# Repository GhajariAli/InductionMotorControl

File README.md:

# InductionMotorControl
Controlling 3 Phase AC Asynchronous Induction Motor

Check [This](https://github.com/GhajariAli/DCMotorControl) Repo for DC motor Control

<details>
<summary> Preparation </summary>
  
  <details>
    
  <summary> Motor Nameplate </summary>

  </details>
  
  <details>
    
  <summary> Designing the circuit </summary>
  
  I've Designed the control boad around this IC fro Infineon [IGCM04F60GAXKMA1](https://www.digikey.ca/en/products/detail/infineon-technologies/IGCM04F60GAXKMA1/5960098)
  
  Here is the video of testing the circuit and getting initial result:
  
   [ ](https://www.youtube.com/shorts/fg0to3o2meA)
  
  So I designed a PCB to get things going Faster, you can find the KiCAD design and initial code to run the motor in [THIS](https://github.com/GhajariAli/InductionMotorControl/tree/FirstCurcuitDesign) branch

  </details>
  
  <details>
    
  <summary> Adding Encoder </summary>
  Induction Motors are usally not controlled by a closed loop using encoder but to validate and verify my own work I'd like to have and encoder on the shaft.
  
  [here](https://www.aliexpress.com/item/4000094589182.html?spm=a2g0o.order_list.order_list_main.56.1fdd1802ZbFUS8) is the encoder I've used : 

  Below is what I've designed to mount the encoder, you'll find all 3D models in the same branch as mentioned in the circuit diagram section.

  Update: had to dessign and print the belt with TPU as it was not standard size turned out good:

  </details>

  <details>
    
  <summary> Testing the PCB </summary>
  PCB came very good. had to change couple resistors and design a base for it:

  and IT WORKS THE FIRST TRY!
  </details>
</details>

<details>
<summary> SPWM speed Control </summary>
  Here is the low and high side signals with only Hi side SPWM:

  and here is the final output 3phase

  this made the motor run smoother, current is now lower and it makes less noise.
  
  This was great but the curent of the motor was not sinusoidal at all.

  Terrible waveform:

  the reason is behind this picture

  so the high and low are not equal value. So it's required to add low side SPWM as well
  Here is the gate signals with all SPWM

  A Closer look

  Here is how the SPWM signals on the High side look after passing through a Filter:

  Now motor current is much more close to sinusoidal current

  here is how the syncronous speed, actual speed and slip looks like in a ramp to 50HZ and coast to stop. as you can see it's not great yet, need to source more voltage (currently only have 60VDC), I believe the V/F control can't go all the way to 50hz with 60 volt.

</details>

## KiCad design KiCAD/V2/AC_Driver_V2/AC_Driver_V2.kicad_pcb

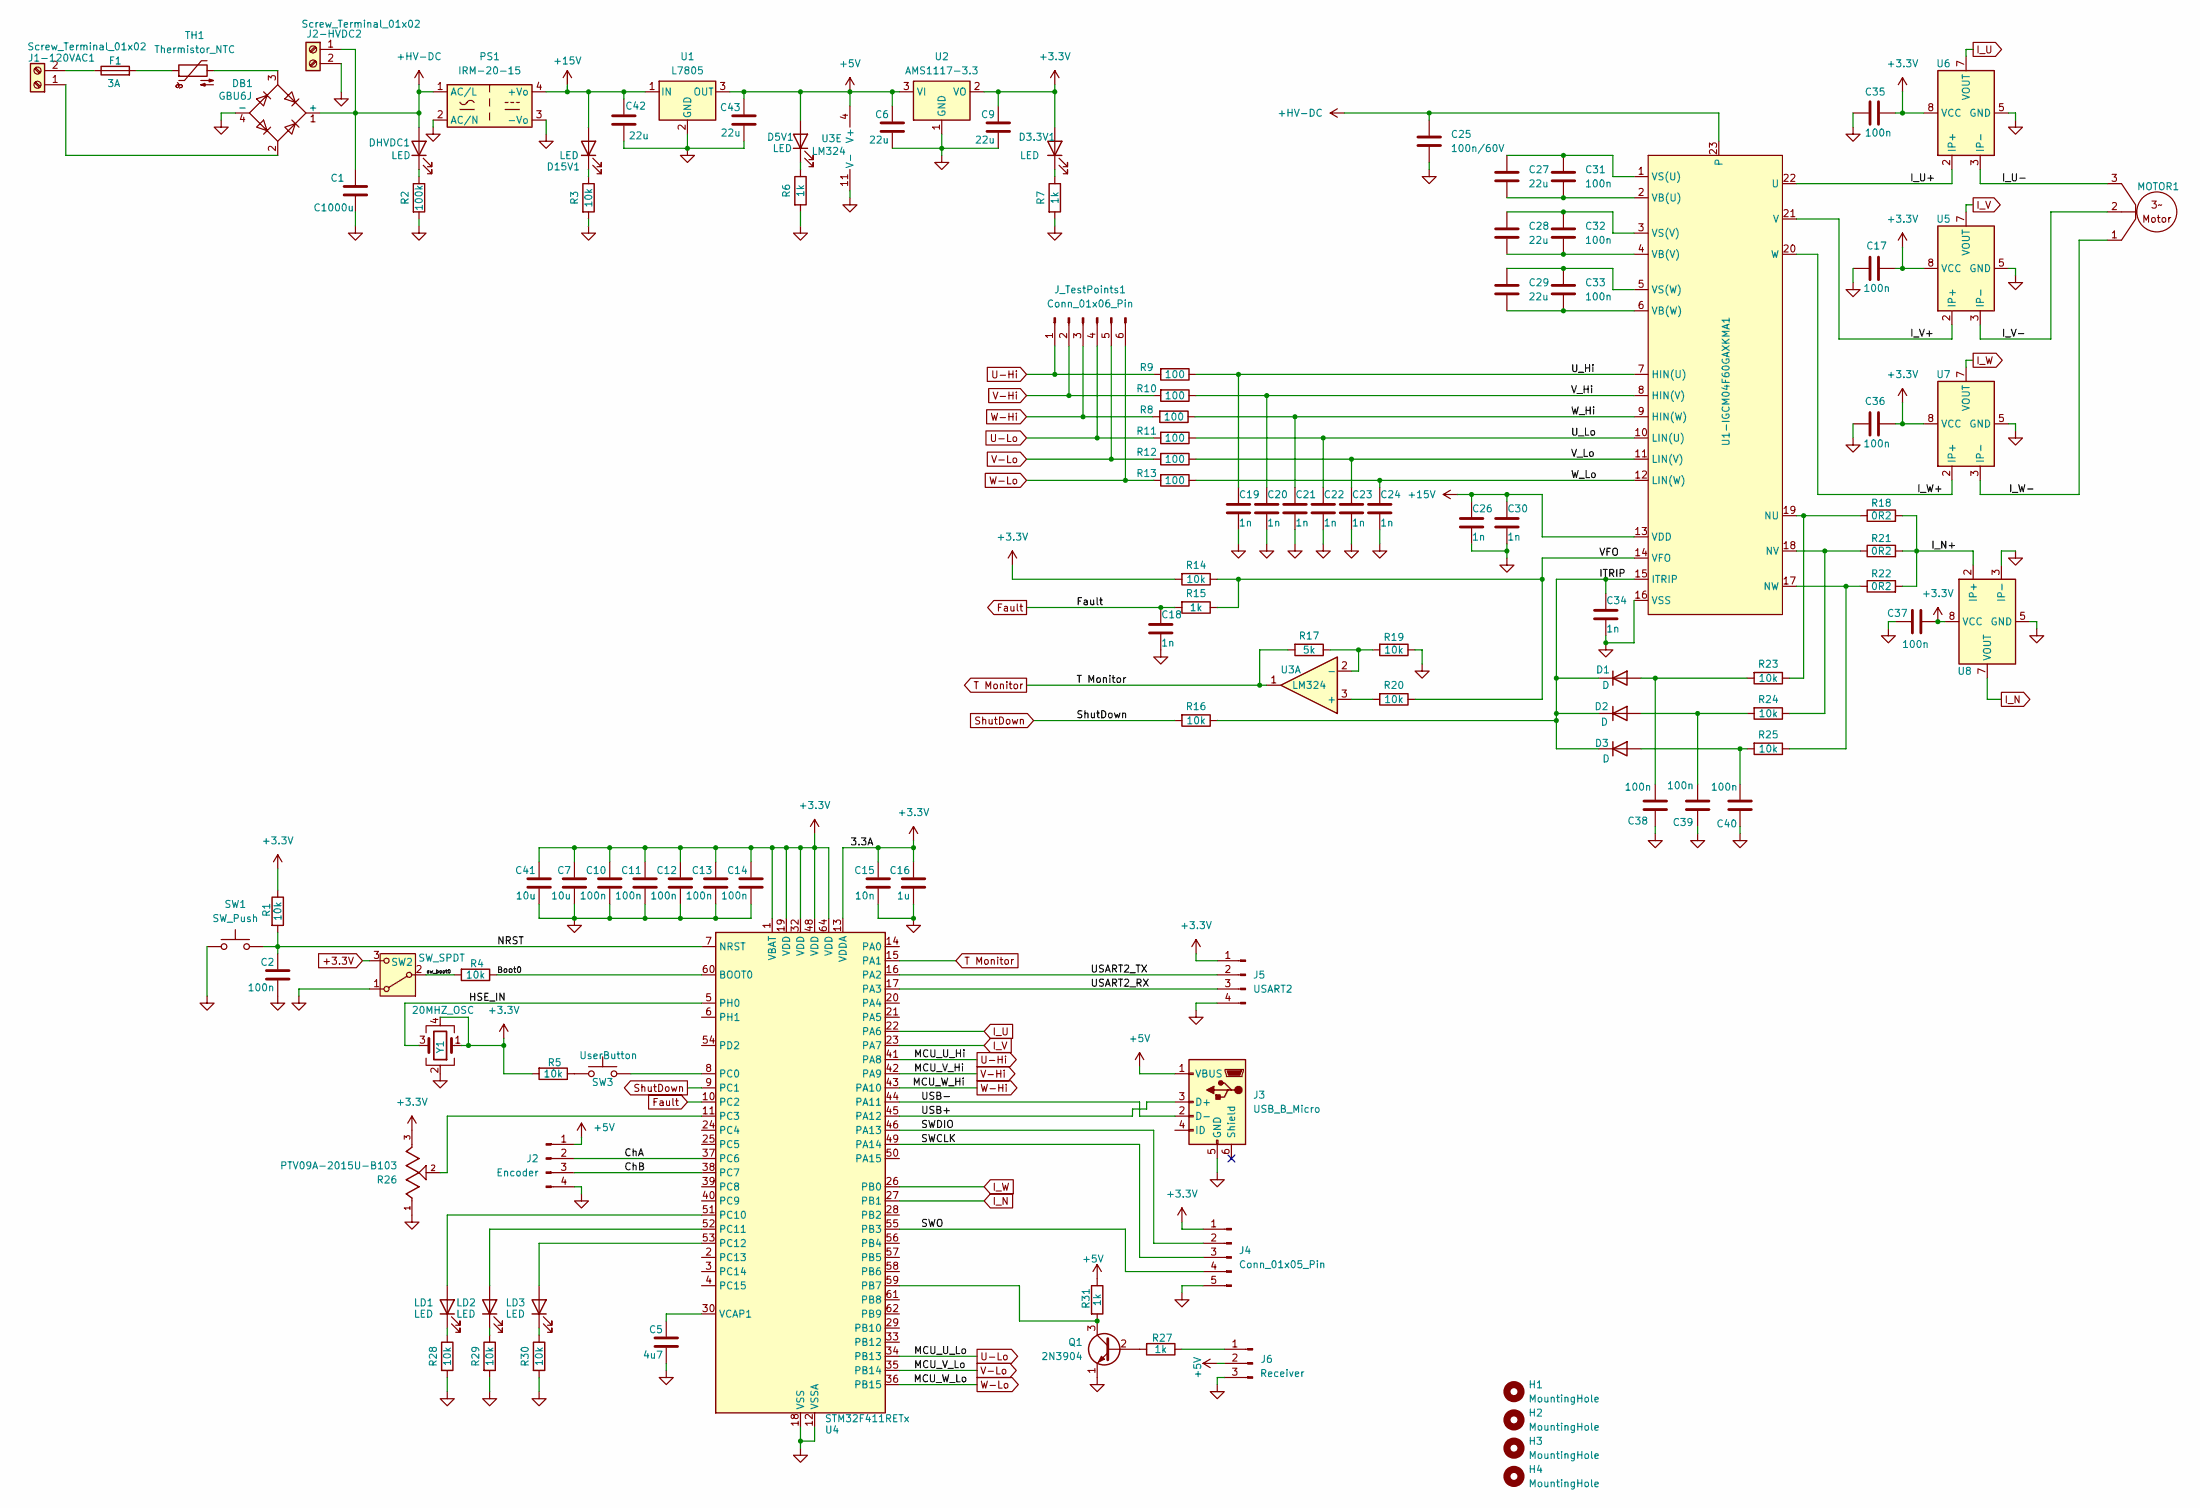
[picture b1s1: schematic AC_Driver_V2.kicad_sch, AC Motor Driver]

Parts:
C1: C1000u; CP_Radial_D22.0mm_P10.00mm_SnapIn
C2, C10, C11, C12, C13, C14, C17, C31, C32, C33, C35, C36, C37, C38, C39, C40: 100n; C_0805_2012Metric
C5: 4u7; C_0805_2012Metric
C6, C9, C42, C43: 22u; C_0805_2012Metric
C7, C41: 10u; C_0805_2012Metric
C15: 10n; C_0805_2012Metric
C16: 1u; C_0805_2012Metric
C18, C19, C20, C21, C22, C23, C24, C26, C30, C34: 1n; C_0805_2012Metric
C25: 100n/60V; C_0805_2012Metric
C27, C28, C29: 22u; C_Radial_D4.0mm_H7.0mm_P1.50mm
D1, D2, D3: D; L_1206_3216Metric
D3.3V1, D5V1, D15V1: LED; LED_0805_2012Metric
DB1: GBU6J; Diode_Bridge_Vishay_GBU
DHVDC1: LED; LED_0805_2012Metric
F1: 3A; L_2512_6332Metric
H1, H2, H3, H4: MountingHole; MountingHole_3.2mm_M3_Pad_Via
J1-120VAC1, J2-HVDC2: Screw_Terminal_01x02; TerminalBlock_Phoenix_PT-1,5-2-5.0-H_1x02_P5.00mm_Horizontal
J2: Encoder; PinHeader_1x04_P2.54mm_Vertical
J3: USB_B_Micro; USB_Micro-B_Amphenol_10103594-0001LF_Horizontal
J4: Conn_01x05_Pin; PinHeader_1x05_P2.54mm_Vertical
J5: USART2; PinHeader_1x04_P2.54mm_Vertical
J6: Receiver; PinHeader_1x03_P2.54mm_Vertical
J_TestPoints1: Conn_01x06_Pin; PinHeader_1x06_P2.54mm_Vertical
LD1, LD2, LD3: LED; LED_0805_2012Metric
MOTOR1: TerminalBlock_Phoenix_PT-1,5-3-5.0-H_1x03_P5.00mm_Horizontal
PS1: IRM-20-15; Converter_ACDC_MeanWell_IRM-20-xx_THT
Q1: 2N3904; TO-92_Inline
R1, R3, R4, R5, R14, R16, R19, R20, R23, R24, R25, R28, R29, R30: 10k; R_0805_2012Metric
R2: 100k; R_0805_2012Metric
R6, R7, R15, R27, R31: 1k; R_0805_2012Metric
R8, R9, R10, R11, R12, R13: 100; R_0805_2012Metric
R17: 5k; R_0805_2012Metric
R18, R21, R22: 0R2; R_Axial_DIN0309_L9.0mm_D3.2mm_P2.54mm_Vertical
R26: PTV09A-2015U-B103; TRIM_PTV09A-2015U-B103; PARTREV 01/20
SW1: SW_Push; SW_Push_1TS009xxxx-xxxx-xxxx_6x6x5mm
SW2: SW_SPDT; SW_SPDT_PCM12
SW3: UserButton; SW_Push_1TS009xxxx-xxxx-xxxx_6x6x5mm
TH1: Thermistor_NTC; R_Axial_DIN0414_L11.9mm_D4.5mm_P7.62mm_Vertical
U1: L7805; TO-263-3_TabPin2
U1-IGCM04F60GAXKMA1: IGCM04F60GAXKMA1
U2: AMS1117-3.3; SOT-223-3_TabPin2
U3: LM324; SSOP-14_5.3x6.2mm_P0.65mm
U4: STM32F411RETx; LQFP-64_10x10mm_P0.5mm
U5, U6, U7, U8: ACS706xLC-05C; SOIC-8_3.9x4.9mm_P1.27mm
Y1: 20MHZ_OSC; Crystal_SMD_Abracon_ABM3C-4Pin_5.0x3.2mm

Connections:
+3.3V: C7.1, C9.1, C10.1, C11.1, C12.1, C13.1, C14.1, C15.1, C16.1, C17.1, C35.1, C36.1, C37.2, C41.1, D3.3V1.2 (A), J4.1, J5.1, R1.1, R5.2, R14.2, R26.3, SW2.3 (C), U2.2 (VO), U4.1 (VBAT), U4.13 (VDDA), U4.19 (VDD), U4.32 (VDD), U4.48 (VDD), U4.64 (VDD), U5.8 (VCC), U6.8 (VCC), U7.8 (VCC), U8.8 (VCC), Y1.1, Y1.4; also elsewhere on the board
+5V: C6.1, C43.1, D5V1.2 (A), J2.1, J3.1 (VBUS), J6.2, R31.1, U1.3 (OUT), U2.3 (VI), U3.4 (V+); also elsewhere on the board
+15V: C26.1, C30.1, C42.1, D15V1.2 (A), PS1.4 (+Vo), U1.1 (IN), U1-IGCM04F60GAXKMA1.13 (VDD); also elsewhere on the board
+HV-DC: C1.1, C25.1, DB1.1 (+), DHVDC1.2 (A), J2-HVDC2.1, PS1.1 (AC/L), U1-IGCM04F60GAXKMA1.23; also elsewhere on the board
/Boot0: R4.1, U4.60 (BOOT0)
/ChA: J2.2, U4.37 (PC6)
/ChB: J2.3, U4.38 (PC7)
/HSE_IN: U4.5 (PH0), Y1.3
/ITRIP: C34.1, D1.1 (K), D2.1 (K), D3.1 (K), R16.1, U1-IGCM04F60GAXKMA1.15 (ITRIP)
/I_N+: R18.2, R21.2, R22.2, U8.1 (IP+), U8.2 (IP+)
/I_U+: U1-IGCM04F60GAXKMA1.22 (U), U6.1 (IP+), U6.2 (IP+)
/I_U-: MOTOR1.3 (W), U6.3 (IP-), U6.4 (IP-)
/I_V+: U1-IGCM04F60GAXKMA1.21 (V), U5.1 (IP+), U5.2 (IP+)
/I_V-: MOTOR1.2 (V), U5.3 (IP-), U5.4 (IP-)
/I_W+: U1-IGCM04F60GAXKMA1.20 (W), U7.1 (IP+), U7.2 (IP+)
/I_W-: MOTOR1.1 (U), U7.3 (IP-), U7.4 (IP-)
/NRST: C2.1, R1.2, SW1.2, U4.7 (NRST)
/SWCLK: J4.3, U4.49 (PA14)
/SWDIO: J4.2, U4.46 (PA13)
/SWO: J4.4, U4.55 (PB3)
/USART2_RX: J5.3, U4.17 (PA3)
/USART2_TX: J5.2, U4.16 (PA2)
/USB+: J3.3 (D+), U4.45 (PA12)
/USB-: J3.2 (D-), U4.44 (PA11)
/U_Hi: C19.1, R9.1, U1-IGCM04F60GAXKMA1.7 (HIN(U))
/U_Lo: C22.1, R11.1, U1-IGCM04F60GAXKMA1.10 (LIN(U))
/VFO: R14.1, R15.1, R20.1, U1-IGCM04F60GAXKMA1.14 (VFO)
/V_Hi: C20.1, R10.1, U1-IGCM04F60GAXKMA1.8 (HIN(V))
/V_Lo: C23.1, R12.1, U1-IGCM04F60GAXKMA1.11 (LIN(V))
/W_Hi: C21.1, R8.1, U1-IGCM04F60GAXKMA1.9 (HIN(W))
/W_Lo: C24.1, R13.1, U1-IGCM04F60GAXKMA1.12 (LIN(W))
/sw_boot0: R4.2, SW2.2 (B)
Fault: C18.1, R15.2, U4.10 (PC2)
GND: C1.2, C2.2, C5.2, C6.2, C7.2, C9.2, C10.2, C11.2, C12.2, C13.2, C14.2, C15.2, C16.2, C17.2, C18.2, C19.2, C20.2, C21.2, C22.2, C23.2, C24.2, C25.2, C26.2, C30.2, C34.2, C35.2, C36.2, C37.1, C38.1, C39.1, C40.1, C41.2, C42.2, C43.2, DB1.4 (-), J2.4, J2-HVDC2.2, J3.5 (GND), J4.5, J5.4, J6.3, PS1.2 (AC/N), PS1.3 (-Vo), Q1.1 (E), R2.2, R3.2, R6.2, R7.2, R19.1, R26.1, R28.2, R29.2, R30.2, SW1.1, SW2.1 (A), U1.2 (GND), U1-IGCM04F60GAXKMA1.16 (VSS), U2.1 (GND), U3.11 (V-), U4.12 (VSSA), U4.18 (VSS), U4.31 (VSS), U4.47 (VSS), U4.63 (VSS), U5.5 (GND), U6.5 (GND), U7.5 (GND), U8.3 (IP-), U8.4 (IP-), U8.5 (GND), Y1.2; also elsewhere on the board
I_N: U4.27 (PB1), U8.7 (VOUT); also elsewhere on the board
I_U: U4.22 (PA6), U6.7 (VOUT); also elsewhere on the board
I_V: U4.23 (PA7), U5.7 (VOUT); also elsewhere on the board
I_W: U4.26 (PB0), U7.7 (VOUT); also elsewhere on the board
unnamed: C38.2, D1.2 (A), R23.2
unnamed: C39.2, D2.2 (A), R24.2
unnamed: C40.2, D3.2 (A), R25.2
unnamed: D3.3V1.1 (K), R7.1
unnamed: D5V1.1 (K), R6.1
unnamed: D15V1.1 (K), R3.1
unnamed: DB1.3, TH1.2
unnamed: DHVDC1.1 (K), R2.1
unnamed: F1.2, TH1.1
unnamed: DB1.2, J1-120VAC1.1
unnamed: F1.1, J1-120VAC1.2
unnamed: J6.1, R27.1
unnamed: LD1.2 (A), U4.51 (PC10)
unnamed: LD1.1 (K), R28.1
unnamed: LD2.2 (A), U4.52 (PC11)
unnamed: LD2.1 (K), R29.1
unnamed: LD3.2 (A), U4.53 (PC12)
unnamed: LD3.1 (K), R30.1
unnamed: Q1.2 (B), R27.2
unnamed: Q1.3 (C), R31.2, U4.59 (PB7)
unnamed: R5.1, SW3.1
unnamed: R18.1, R23.1, U1-IGCM04F60GAXKMA1.19 (NU)
unnamed: R21.1, R24.1, U1-IGCM04F60GAXKMA1.18 (NV)
unnamed: R22.1, R25.1, U1-IGCM04F60GAXKMA1.17 (NW)
unnamed: C27.2, C31.2, U1-IGCM04F60GAXKMA1.2 (VB(U))
unnamed: C28.2, C32.2, U1-IGCM04F60GAXKMA1.4 (VB(V))
unnamed: C29.2, C33.2, U1-IGCM04F60GAXKMA1.6 (VB(W))
unnamed: C27.1, C31.1, U1-IGCM04F60GAXKMA1.1 (VS(U))
unnamed: C28.1, C32.1, U1-IGCM04F60GAXKMA1.3 (VS(V))
unnamed: C29.1, C33.1, U1-IGCM04F60GAXKMA1.5 (VS(W))
unnamed: R20.2, U3.3 (+)
unnamed: R17.1, R19.2, U3.2 (-)
unnamed: SW3.2, U4.8 (PC0)
unnamed: R26.2, U4.11 (PC3)
unnamed: C5.1, U4.30 (VCAP1)
ShutDown: R16.2, U4.9 (PC1)
T Monitor: R17.2, U3.1, U4.15 (PA1)
U-Hi: J_TestPoints1.1, R9.2, U4.41 (PA8)
U-Lo: J_TestPoints1.4, R11.2, U4.34 (PB13)
V-Hi: J_TestPoints1.2, R10.2, U4.42 (PA9)
V-Lo: J_TestPoints1.5, R12.2, U4.35 (PB14)
W-Hi: J_TestPoints1.3, R8.2, U4.43 (PA10)
W-Lo: J_TestPoints1.6, R13.2, U4.36 (PB15)

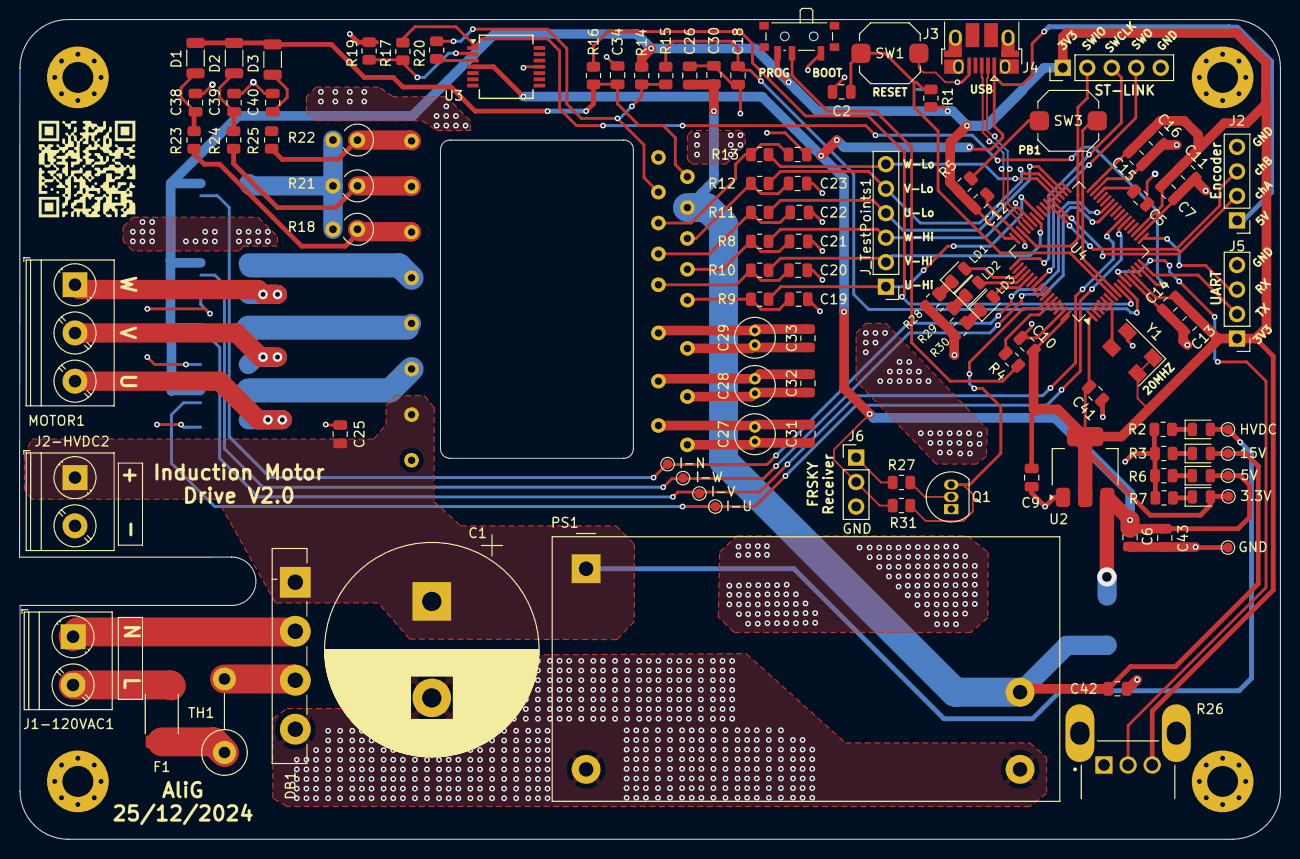
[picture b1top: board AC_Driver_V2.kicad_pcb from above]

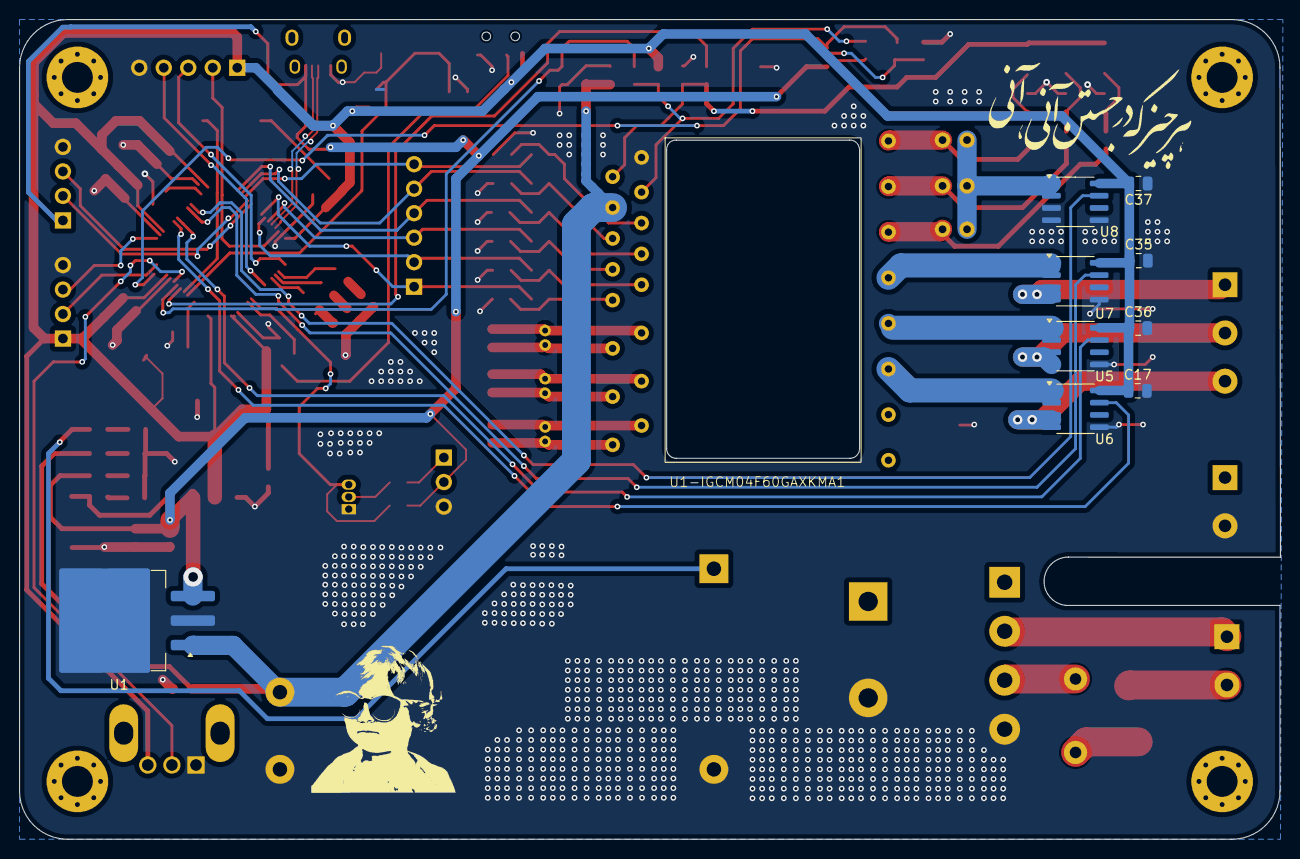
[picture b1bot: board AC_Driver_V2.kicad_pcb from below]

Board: 2 copper layers, 130.8 x 85.0 mm, 121 parts (10 on the bottom side), 81 nets.

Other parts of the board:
3.3V, 5V, 15V: TestPoint_Pad_D1.0mm
GND: TestPoint_Pad_D1.0mm
HVDC: TestPoint_Pad_D1.0mm
I-N: TestPoint_Pad_D1.0mm
I-U: TestPoint_Pad_D1.0mm
I-V: TestPoint_Pad_D1.0mm
I-W: TestPoint_Pad_D1.0mm

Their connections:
+3.3V: 3.3V.1; also elsewhere on the board
+5V: 5V.1; also elsewhere on the board
+15V: 15V.1; also elsewhere on the board
+HV-DC: HVDC.1; also elsewhere on the board
GND: GND.1; also elsewhere on the board
I_N: I-N.1; also elsewhere on the board
I_U: I-U.1; also elsewhere on the board
I_V: I-V.1; also elsewhere on the board
I_W: I-W.1; also elsewhere on the board

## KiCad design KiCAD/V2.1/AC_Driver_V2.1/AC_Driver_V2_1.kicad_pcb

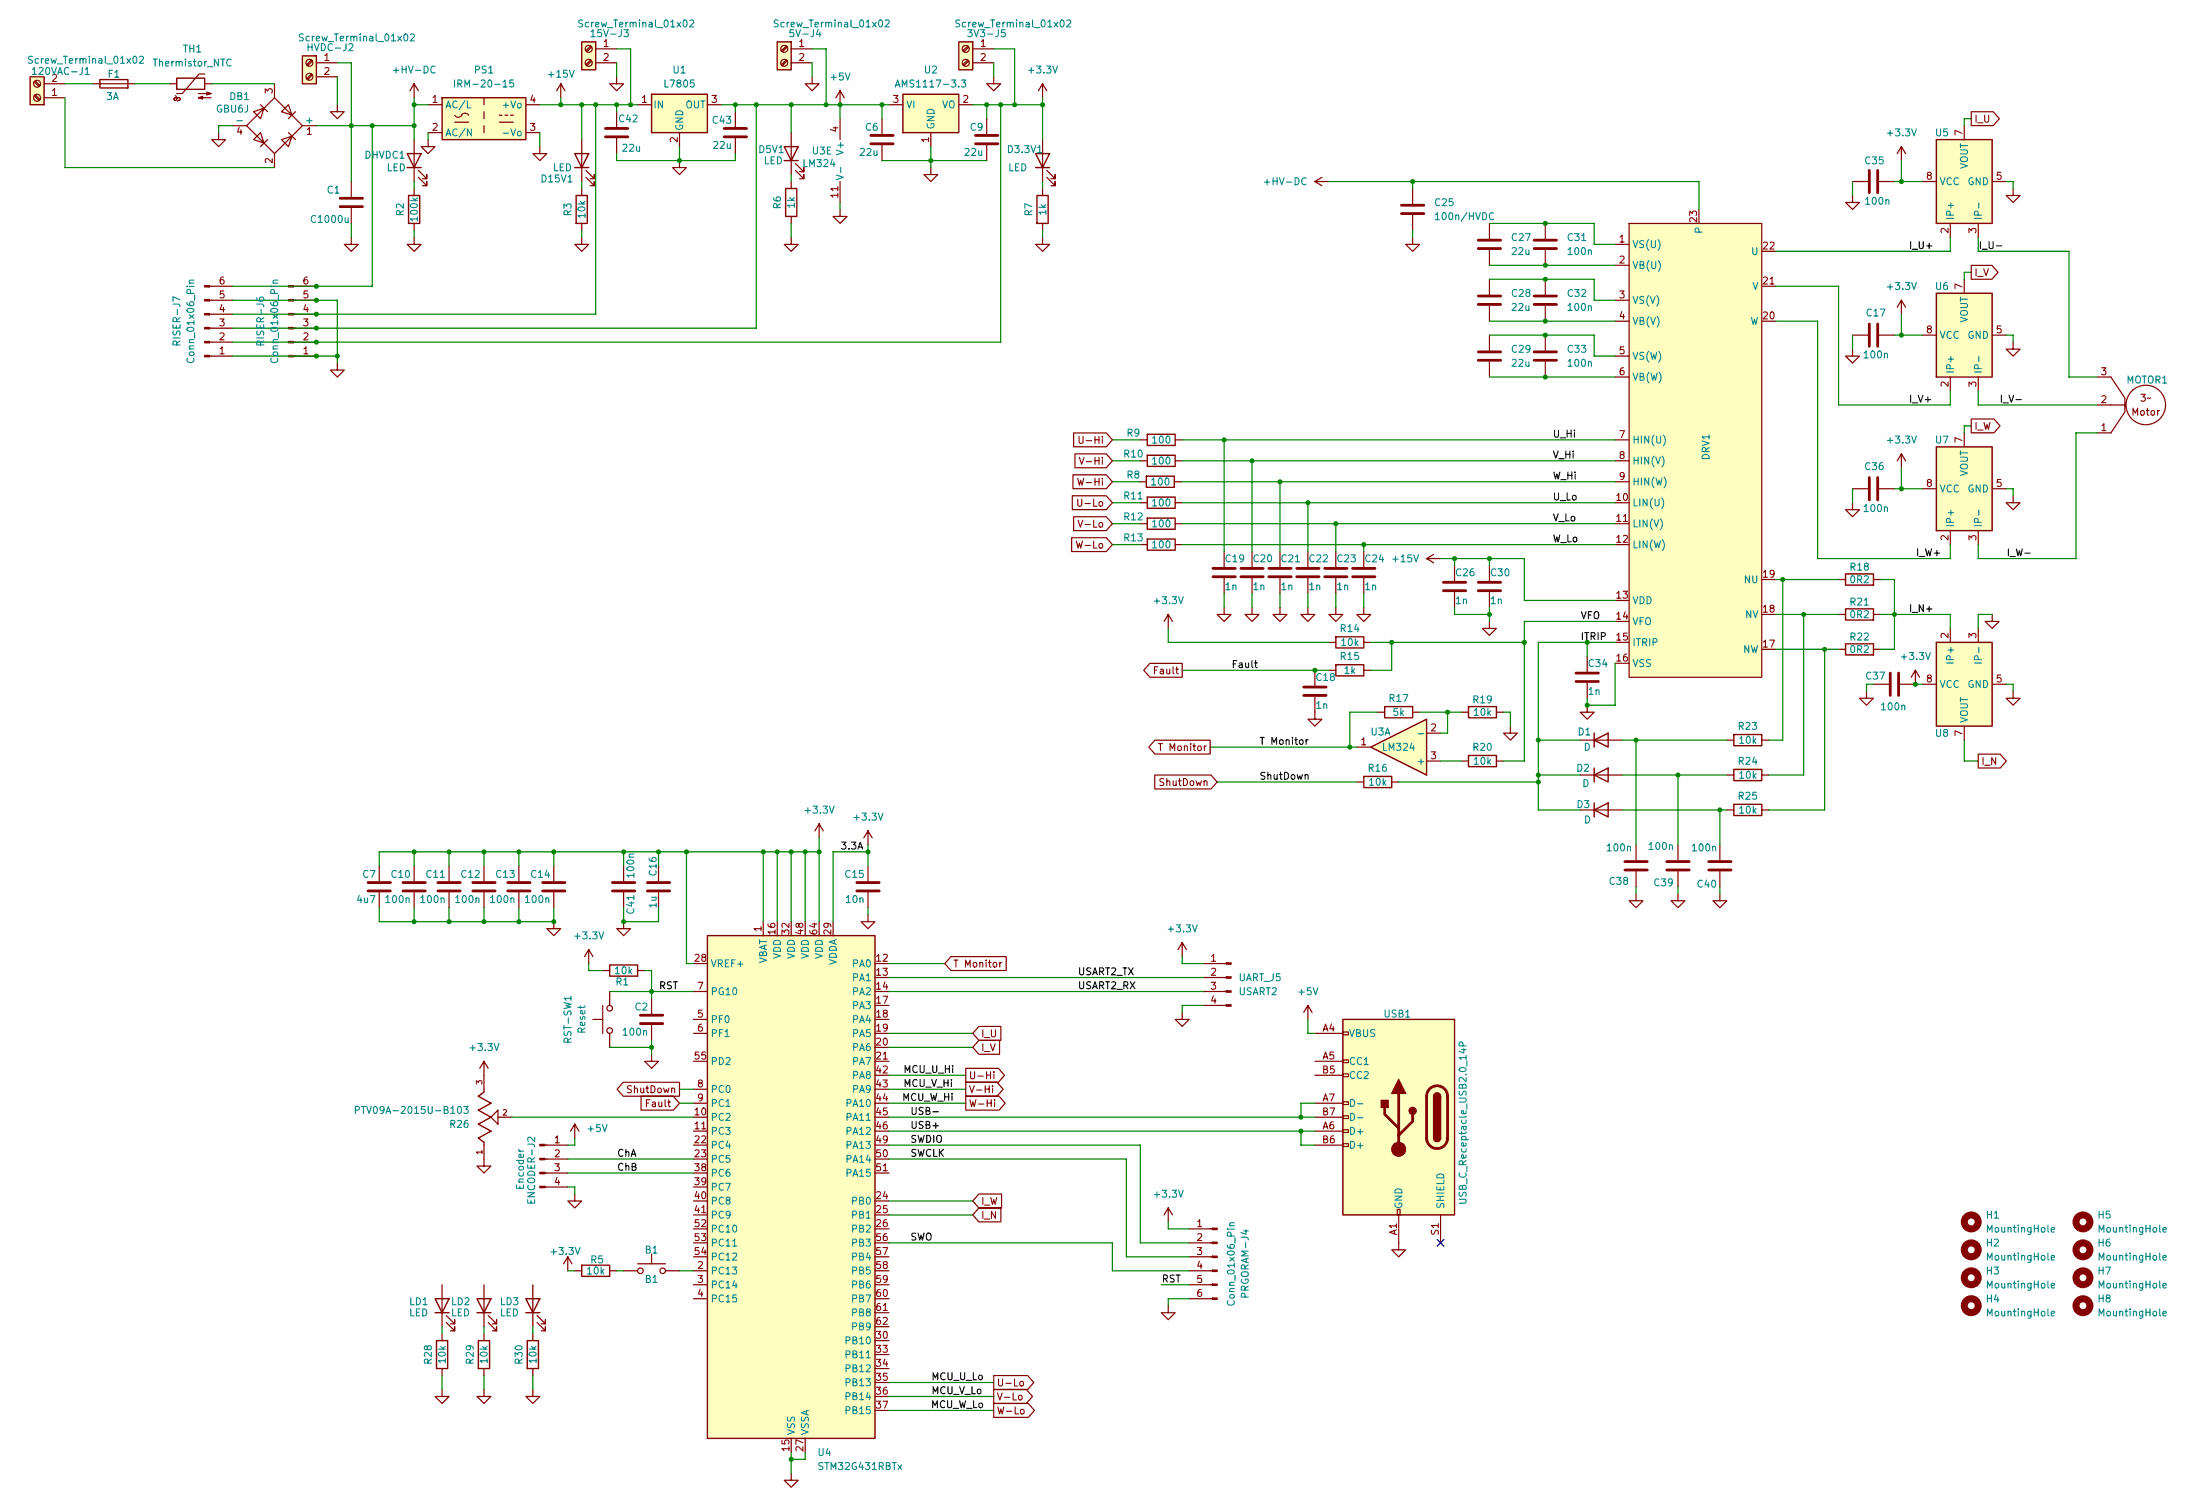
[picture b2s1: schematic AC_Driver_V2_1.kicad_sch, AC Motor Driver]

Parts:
3V3-J5, 5V-J4, 15V-J3, 120VAC-J1: Screw_Terminal_01x02; TerminalBlock_Phoenix_PT-1,5-2-5.0-H_1x02_P5.00mm_Horizontal
B1: B1; SW_Push_1TS009xxxx-xxxx-xxxx_6x6x5mm
C1: C1000u; CP_Radial_D22.0mm_P10.00mm_SnapIn
C2, C10, C11, C12, C13, C14, C17, C31, C32, C33, C35, C36, C37, C38, C39, C40, C41: 100n; C_0805_2012Metric
C6, C9, C42, C43: 22u; C_0805_2012Metric
C7: 4u7; C_0805_2012Metric
C15: 10n; C_0805_2012Metric
C16: 1u; C_0805_2012Metric
C18, C19, C20, C21, C22, C23, C24, C26, C30, C34: 1n; C_0805_2012Metric
C25: 100n/HVDC; C_0805_2012Metric
C27, C28, C29: 22u; C_Radial_D4.0mm_H7.0mm_P1.50mm
D1, D2, D3: D; L_1206_3216Metric
D3.3V1, D5V1, D15V1: LED; LED_0805_2012Metric
DB1: GBU6J; Diode_Bridge_Vishay_GBU
DHVDC1: LED; LED_0805_2012Metric
DRV1: IGCM04F60GAXKMA1
ENCODER-J2: Encoder; PinHeader_1x04_P2.54mm_Vertical
F1: 3A; L_2512_6332Metric
H1, H2, H3, H4, H5, H6, H7, H8: MountingHole; MountingHole_3.2mm_M3_Pad_Via
HVDC-J2: Screw_Terminal_01x02; TerminalBlock_Phoenix_PT-1,5-2-5.0-H_1x02_P5.00mm_Horizontal
LD1, LD2, LD3: LED; LED_0805_2012Metric
MOTOR1: TerminalBlock_Phoenix_PT-1,5-3-5.0-H_1x03_P5.00mm_Horizontal
PRGORAM-J4: Conn_01x06_Pin; PinHeader_1x06_P2.54mm_Vertical
PS1: IRM-20-15; Converter_ACDC_MeanWell_IRM-20-xx_THT
R1, R3, R5, R14, R16, R19, R20, R23, R24, R25, R28, R29, R30: 10k; R_0805_2012Metric
R2: 100k; R_0805_2012Metric
R6, R7, R15: 1k; R_0805_2012Metric
R8, R9, R10, R11, R12, R13: 100; R_0805_2012Metric
R17: 5k; R_0805_2012Metric
R18, R21, R22: 0R2; R_Axial_DIN0309_L9.0mm_D3.2mm_P2.54mm_Vertical
R26: PTV09A-2015U-B103; TRIM_PTV09A-2015U-B103; PARTREV 01/20
RISER-J6, RISER-J7: Conn_01x06_Pin; PinHeader_1x06_P2.54mm_Vertical
RST-SW1: Reset; SW_Push_1TS009xxxx-xxxx-xxxx_6x6x5mm
TH1: Thermistor_NTC; R_Axial_DIN0414_L11.9mm_D4.5mm_P7.62mm_Vertical
U1: L7805; TO-263-3_TabPin2
U2: AMS1117-3.3; SOT-223-3_TabPin2
U3: LM324; SSOP-14_5.3x6.2mm_P0.65mm
U4: STM32G431RBTx; LQFP-64_10x10mm_P0.5mm
U5, U6, U7, U8: ACS706xLC-05C; SOIC-8_3.9x4.9mm_P1.27mm
UART_J5: USART2; PinHeader_1x04_P2.54mm_Vertical
USB1: USB_C_Receptacle_USB2.0_14P; USB_C_Receptacle_GCT_USB4105-xx-A_16P_TopMnt_Horizontal

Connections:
+3.3V: 3V3-J5.1, C7.1, C9.1, C10.1, C11.1, C12.1, C13.1, C14.1, C15.1, C16.1, C17.1, C35.1, C36.1, C37.2, C41.2, D3.3V1.2 (A), PRGORAM-J4.1, R1.1, R5.2, R14.2, R26.3, RISER-J6.2, RISER-J7.2, U2.2 (VO), U4.1 (VBAT), U4.16 (VDD), U4.28 (VREF+), U4.29 (VDDA), U4.32 (VDD), U4.48 (VDD), U4.64 (VDD), U5.8 (VCC), U6.8 (VCC), U7.8 (VCC), U8.8 (VCC), UART_J5.1
+5V: 5V-J4.1, C6.1, C43.1, D5V1.2 (A), ENCODER-J2.1, RISER-J6.3, RISER-J7.3, U1.3 (OUT), U2.3 (VI), U3.4 (V+), USB1.A4 (VBUS), USB1.A9 (VBUS), USB1.B4 (VBUS), USB1.B9 (VBUS)
+15V: 15V-J3.1, C26.1, C30.1, C42.1, D15V1.2 (A), DRV1.13 (VDD), PS1.4 (+Vo), RISER-J6.4, RISER-J7.4, U1.1 (IN)
+HV-DC: C1.1, C25.1, DB1.1 (+), DHVDC1.2 (A), DRV1.23, HVDC-J2.1, PS1.1 (AC/L), RISER-J6.6, RISER-J7.6
/ChA: ENCODER-J2.2, U4.23 (PC5)
/ChB: ENCODER-J2.3, U4.38 (PC6)
/ITRIP: C34.1, D1.1 (K), D2.1 (K), D3.1 (K), DRV1.15 (ITRIP), R16.1
/I_N+: R18.2, R21.2, R22.2, U8.1 (IP+), U8.2 (IP+)
/I_U+: DRV1.22 (U), U5.1 (IP+), U5.2 (IP+)
/I_U-: MOTOR1.3 (W), U5.3 (IP-), U5.4 (IP-)
/I_V+: DRV1.21 (V), U6.1 (IP+), U6.2 (IP+)
/I_V-: MOTOR1.2 (V), U6.3 (IP-), U6.4 (IP-)
/I_W+: DRV1.20 (W), U7.1 (IP+), U7.2 (IP+)
/I_W-: MOTOR1.1 (U), U7.3 (IP-), U7.4 (IP-)
/RST: C2.1, PRGORAM-J4.5, R1.2, RST-SW1.2, U4.7 (PG10)
/SWCLK: PRGORAM-J4.3, U4.50 (PA14)
/SWDIO: PRGORAM-J4.2, U4.49 (PA13)
/SWO: PRGORAM-J4.4, U4.56 (PB3)
/USART2_RX: U4.14 (PA2), UART_J5.3
/USART2_TX: U4.13 (PA1), UART_J5.2
/USB+: U4.46 (PA12), USB1.A6 (D+), USB1.B6 (D+)
/USB-: U4.45 (PA11), USB1.A7 (D-), USB1.B7 (D-)
/U_Hi: C19.1, DRV1.7 (HIN(U)), R9.1
/U_Lo: C22.1, DRV1.10 (LIN(U)), R11.1
/VFO: DRV1.14 (VFO), R14.1, R15.1, R20.1
/V_Hi: C20.1, DRV1.8 (HIN(V)), R10.1
/V_Lo: C23.1, DRV1.11 (LIN(V)), R12.1
/W_Hi: C21.1, DRV1.9 (HIN(W)), R8.1
/W_Lo: C24.1, DRV1.12 (LIN(W)), R13.1
Fault: C18.1, R15.2, U4.9 (PC1)
GND: 3V3-J5.2, 5V-J4.2, 15V-J3.2, C1.2, C2.2, C6.2, C7.2, C9.2, C10.2, C11.2, C12.2, C13.2, C14.2, C15.2, C16.2, C17.2, C18.2, C19.2, C20.2, C21.2, C22.2, C23.2, C24.2, C25.2, C26.2, C30.2, C34.2, C35.2, C36.2, C37.1, C38.1, C39.1, C40.1, C41.1, C42.2, C43.2, DB1.4 (-), DRV1.16 (VSS), ENCODER-J2.4, HVDC-J2.2, PRGORAM-J4.6, PS1.2 (AC/N), PS1.3 (-Vo), R2.2, R3.2, R6.2, R7.2, R19.1, R26.1, R28.2, R29.2, R30.2, RISER-J6.1, RISER-J6.5, RISER-J7.1, RISER-J7.5, RST-SW1.1, U1.2 (GND), U2.1 (GND), U3.11 (V-), U4.15 (VSS), U4.27 (VSSA), U4.31 (VSS), U4.47 (VSS), U4.63 (VSS), U5.5 (GND), U6.5 (GND), U7.5 (GND), U8.3 (IP-), U8.4 (IP-), U8.5 (GND), UART_J5.4, USB1.A1 (GND), USB1.A12 (GND), USB1.B1 (GND), USB1.B12 (GND)
I_N: U4.25 (PB1), U8.7 (VOUT)
I_U: U4.19 (PA5), U5.7 (VOUT)
I_V: U4.20 (PA6), U6.7 (VOUT)
I_W: U4.24 (PB0), U7.7 (VOUT)
unnamed: 120VAC-J1.1, DB1.2
unnamed: 120VAC-J1.2, F1.1
unnamed: B1.1, R5.1
unnamed: C38.2, D1.2 (A), R23.2
unnamed: C39.2, D2.2 (A), R24.2
unnamed: C40.2, D3.2 (A), R25.2
unnamed: D3.3V1.1 (K), R7.1
unnamed: D5V1.1 (K), R6.1
unnamed: D15V1.1 (K), R3.1
unnamed: DB1.3, TH1.2
unnamed: DHVDC1.1 (K), R2.1
unnamed: DRV1.19 (NU), R18.1, R23.1
unnamed: DRV1.18 (NV), R21.1, R24.1
unnamed: DRV1.17 (NW), R22.1, R25.1
unnamed: C27.2, C31.2, DRV1.2 (VB(U))
unnamed: C28.2, C32.2, DRV1.4 (VB(V))
unnamed: C29.2, C33.2, DRV1.6 (VB(W))
unnamed: C27.1, C31.1, DRV1.1 (VS(U))
unnamed: C28.1, C32.1, DRV1.3 (VS(V))
unnamed: C29.1, C33.1, DRV1.5 (VS(W))
unnamed: F1.2, TH1.1
unnamed: LD1.1 (K), R28.1
unnamed: LD2.1 (K), R29.1
unnamed: LD3.1 (K), R30.1
unnamed: R20.2, U3.3 (+)
unnamed: R17.1, R19.2, U3.2 (-)
unnamed: R26.2, U4.10 (PC2)
unnamed: B1.2, U4.2 (PC13)
ShutDown: R16.2, U4.8 (PC0)
T Monitor: R17.2, U3.1, U4.12 (PA0)
U-Hi: R9.2, U4.42 (PA8)
U-Lo: R11.2, U4.35 (PB13)
V-Hi: R10.2, U4.43 (PA9)
V-Lo: R12.2, U4.36 (PB14)
W-Hi: R8.2, U4.44 (PA10)
W-Lo: R13.2, U4.37 (PB15)

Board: 4 copper layers, 112 parts (13 on the bottom side), 71 nets, no tracks yet.

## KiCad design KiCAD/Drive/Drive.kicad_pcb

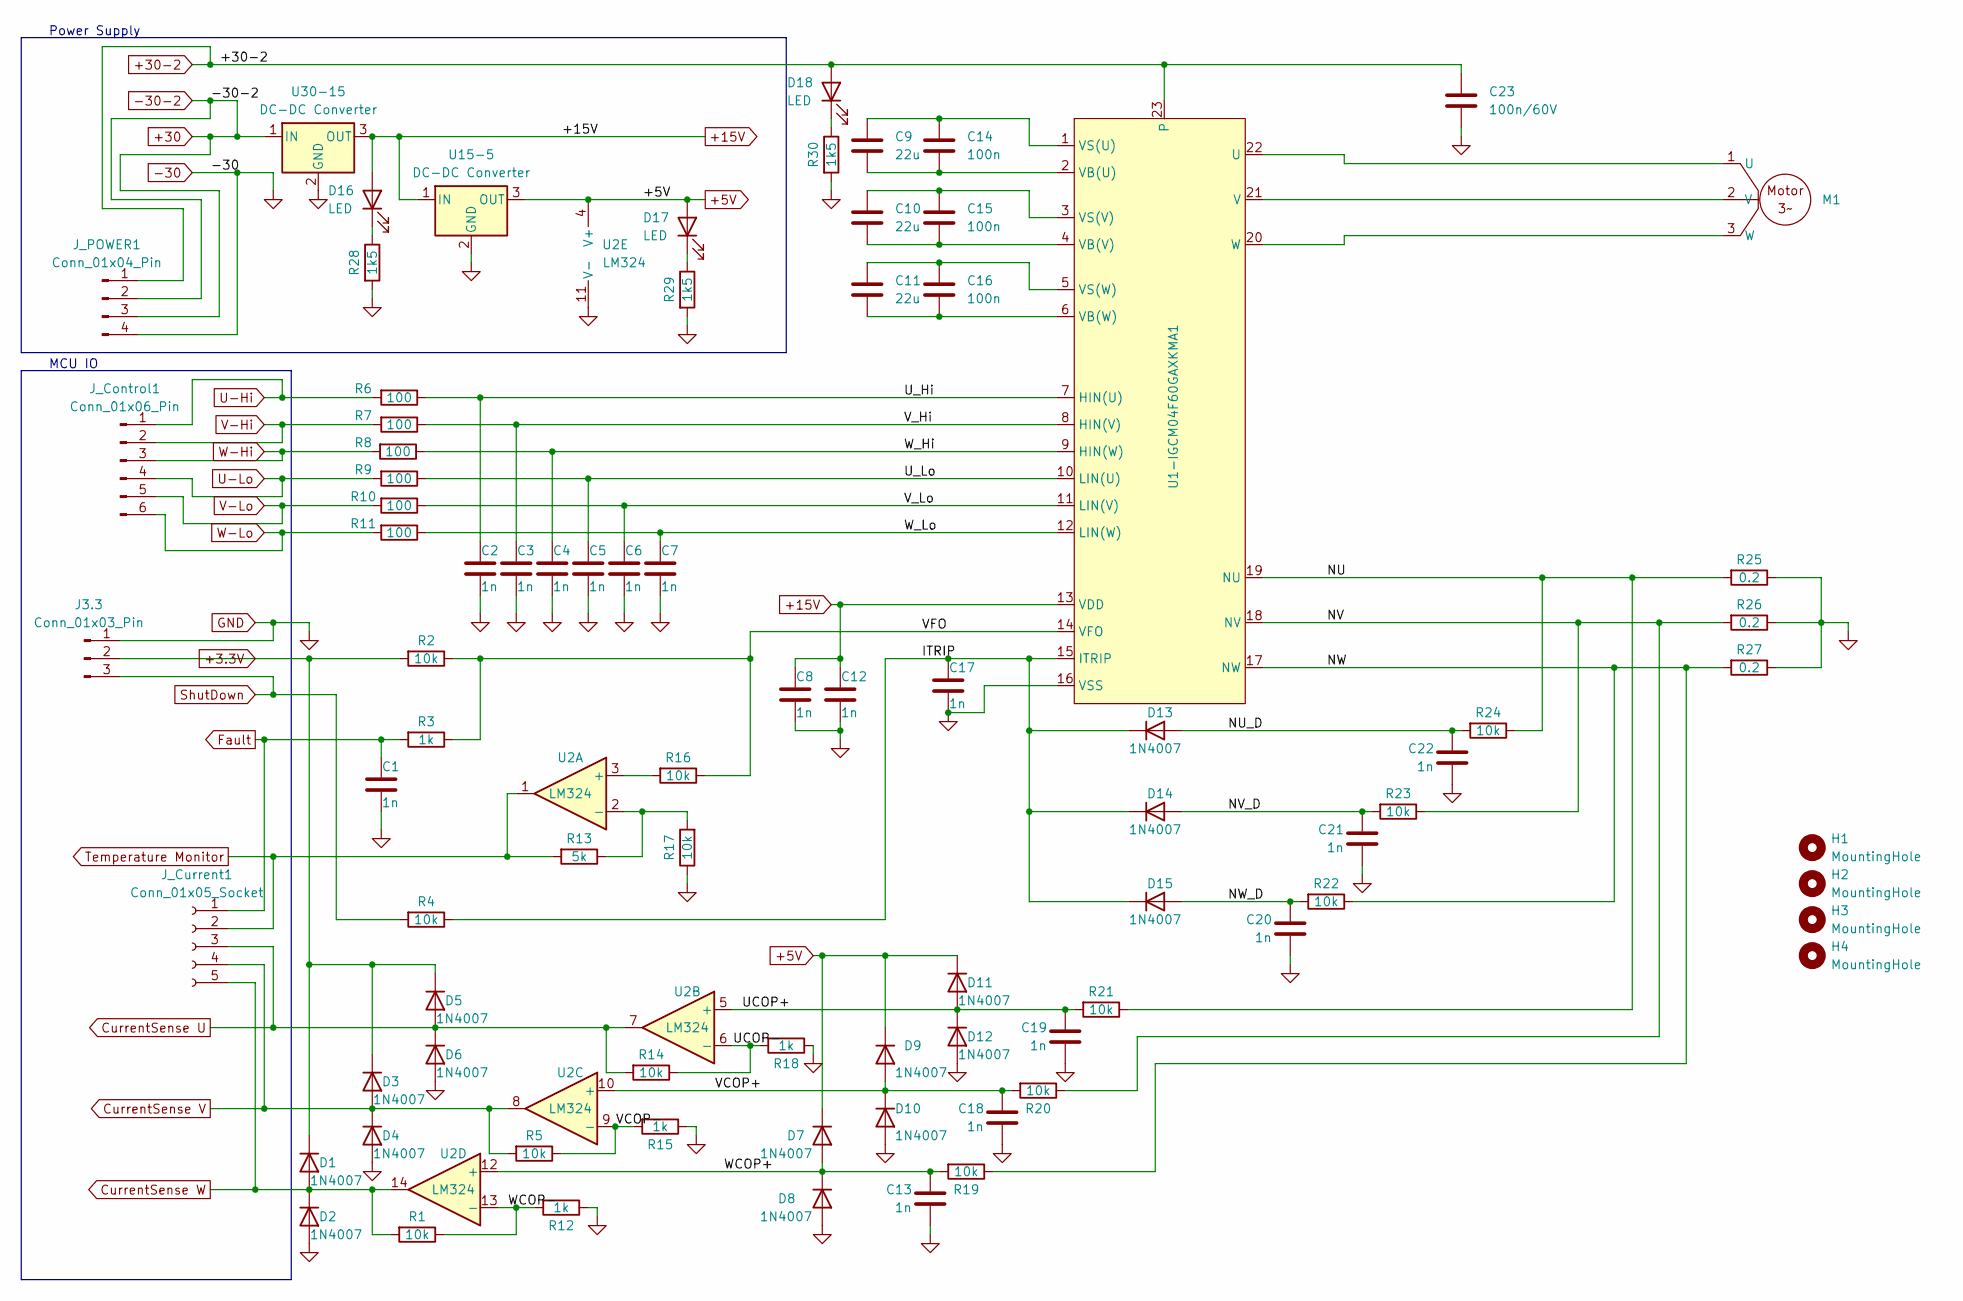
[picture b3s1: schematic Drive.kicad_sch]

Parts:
C1, C2, C3, C4, C5, C6, C7, C8, C12, C13, C17, C18, C19, C20, C21, C22: 1n; C_1206_3216Metric
C9, C10, C11: 22u; C_Radial_D4.0mm_H7.0mm_P1.50mm
C14, C15, C16: 100n; C_1206_3216Metric
C23: 100n/60V; C_1206_3216Metric
D1, D2, D3, D4, D5, D6, D7, D8, D9, D10, D11, D12, D13, D14, D15: 1N4007; D_SOD-323
D16, D17, D18: LED; LED_1206_3216Metric
H1, H2, H3, H4: MountingHole; MountingHole_3.5mm
J3.3: Conn_01x03_Pin; PinHeader_1x03_P2.54mm_Vertical
J_Control1: Conn_01x06_Pin; PinHeader_1x06_P2.54mm_Vertical
J_Current1: Conn_01x05_Socket; PinHeader_1x05_P2.54mm_Vertical
J_POWER1: Conn_01x04_Pin; PinHeader_1x04_P2.54mm_Vertical
M1: PinHeader_1x03_P2.54mm_Vertical
R1, R2, R4, R5, R14, R16, R17, R19, R20, R21, R22, R23, R24: 10k; R_1206_3216Metric
R3, R12, R15, R18: 1k; R_1206_3216Metric
R6, R7, R8, R9, R10, R11: 100; R_1206_3216Metric
R13: 5k; R_1206_3216Metric
R25, R26, R27: 0.2; R_Axial_DIN0204_L3.6mm_D1.6mm_P1.90mm_Vertical
R28, R29, R30: 1k5; R_1206_3216Metric
U1-IGCM04F60GAXKMA1: IGCM04F60GAXKMA1
U2: LM324; SSOP-14_5.3x6.2mm_P0.65mm
U15-5, U30-15: DC-DC Converter; PinHeader_1x03_P2.54mm_Vertical

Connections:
+3.3V: D1.1 (K), D3.1 (K), D5.1 (K), J3.3.2, R2.2
+5V: D7.1 (K), D9.1 (K), D11.1 (K), D17.2 (A), U2.4 (V+), U15-5.3 (OUT)
+15V: C8.1, C12.1, D16.2 (A), U1-IGCM04F60GAXKMA1.13 (VDD), U15-5.1 (IN), U30-15.3 (OUT)
+30: J_POWER1.2, J_POWER1.3, U30-15.1 (IN)
+30-2: C23.1, D18.2 (A), J_POWER1.1, U1-IGCM04F60GAXKMA1.23
-30: C1.2, C2.2, C3.2, C4.2, C5.2, C6.2, C7.2, C8.2, C12.2, C13.2, C17.2, C18.2, C19.2, C20.2, C21.2, C22.2, C23.2, D2.2 (A), D4.2 (A), D6.2 (A), D8.2 (A), D10.2 (A), D12.2 (A), J3.3.1, J_POWER1.4, R12.1, R15.1, R17.1, R18.1, R25.1, R26.1, R27.1, R28.2, R29.2, R30.2, U1-IGCM04F60GAXKMA1.16 (VSS), U2.11 (V-), U15-5.2 (GND), U30-15.2 (GND)
/ITRIP: C17.1, D13.1 (K), D14.1 (K), D15.1 (K), R4.1, U1-IGCM04F60GAXKMA1.15 (ITRIP)
/NU: R21.1, R24.1, R25.2, U1-IGCM04F60GAXKMA1.19 (NU)
/NU_D: C22.1, D13.2 (A), R24.2
/NV: R20.1, R23.1, R26.2, U1-IGCM04F60GAXKMA1.18 (NV)
/NV_D: C21.1, D14.2 (A), R23.2
/NW: R19.1, R22.1, R27.2, U1-IGCM04F60GAXKMA1.17 (NW)
/NW_D: C20.1, D15.2 (A), R22.2
/UCOP+: C19.1, D11.2 (A), D12.1 (K), R21.2, U2.5 (+)
/UCOP-: R14.1, R18.2, U2.6 (-)
/U_Hi: C2.1, R6.1, U1-IGCM04F60GAXKMA1.7 (HIN(U))
/U_Lo: C5.1, R9.1, U1-IGCM04F60GAXKMA1.10 (LIN(U))
/VCOP+: C18.1, D9.2 (A), D10.1 (K), R20.2, U2.10 (+)
/VCOP-: R5.1, R15.2, U2.9 (-)
/VFO: R2.1, R3.1, R16.1, U1-IGCM04F60GAXKMA1.14 (VFO)
/V_Hi: C3.1, R7.1, U1-IGCM04F60GAXKMA1.8 (HIN(V))
/V_Lo: C6.1, R10.1, U1-IGCM04F60GAXKMA1.11 (LIN(V))
/WCOP+: C13.1, D7.2 (A), D8.1 (K), R19.2, U2.12 (+)
/WCOP-: R1.1, R12.2, U2.13 (-)
/W_Hi: C4.1, R8.1, U1-IGCM04F60GAXKMA1.9 (HIN(W))
/W_Lo: C7.1, R11.1, U1-IGCM04F60GAXKMA1.12 (LIN(W))
CurrentSense U: D5.2 (A), D6.1 (K), J_Current1.3, R14.2, U2.7
CurrentSense V: D3.2 (A), D4.1 (K), J_Current1.4, R5.2, U2.8
CurrentSense W: D1.2 (A), D2.1 (K), J_Current1.5, R1.2, U2.14
Fault: C1.1, J_Current1.1, R3.2
unnamed: D16.1 (K), R28.1
unnamed: D17.1 (K), R29.1
unnamed: D18.1 (K), R30.1
unnamed: M1.1 (U), U1-IGCM04F60GAXKMA1.22 (U)
unnamed: M1.2 (V), U1-IGCM04F60GAXKMA1.21 (V)
unnamed: M1.3 (W), U1-IGCM04F60GAXKMA1.20 (W)
unnamed: C9.2, C14.2, U1-IGCM04F60GAXKMA1.2 (VB(U))
unnamed: C10.2, C15.2, U1-IGCM04F60GAXKMA1.4 (VB(V))
unnamed: C11.2, C16.2, U1-IGCM04F60GAXKMA1.6 (VB(W))
unnamed: C9.1, C14.1, U1-IGCM04F60GAXKMA1.1 (VS(U))
unnamed: C10.1, C15.1, U1-IGCM04F60GAXKMA1.3 (VS(V))
unnamed: C11.1, C16.1, U1-IGCM04F60GAXKMA1.5 (VS(W))
unnamed: R16.2, U2.3 (+)
unnamed: R13.1, R17.2, U2.2 (-)
ShutDown: J3.3.3, R4.2
Temperature Monitor: J_Current1.2, R13.2, U2.1
U-Hi: J_Control1.1, R6.2
U-Lo: J_Control1.4, R9.2
V-Hi: J_Control1.2, R7.2
V-Lo: J_Control1.5, R10.2
W-Hi: J_Control1.3, R8.2
W-Lo: J_Control1.6, R11.2

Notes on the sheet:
MCU IO
Power Supply
